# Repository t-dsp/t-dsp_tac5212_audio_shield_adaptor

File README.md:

# T-DSP TAC5212 Audio Shield Adaptor for Teensy 4.1

**Part of the [T-DSP](https://t-dsp.com) open modular audio platform.**

A compact carrier board (60.93mm × 26.46mm) that connects a [T-DSP TAC5212 audio module](https://github.com/t-dsp) and a [Teensy 4.1](https://www.pjrc.com/teensy/) together into a simple, USB-powered Teensy audio shield — with stereo line in/out, two onboard PDM MEMS microphones, USB Host, and SD card access.

| | |
|:---:|:---:|
|  |  |
|  |  |

**[View 3D Render Gallery](https://t-dsp.github.io/t-dsp_tac5212_audio_shield_adaptor/gallery.html)** -- interactive slideshow of all board views

## Assembled Hardware

| | |
|:---:|:---:|
|  |  |
| Top — TAC5212 module on the adaptor | Side — adaptor + Teensy 4.1 + TAC5212 module |

## What It Is

This is the simplest board in the T-DSP ecosystem. It is an **adaptor** — a small carrier PCB that brings together two modules:

- **[T-DSP TAC5212 module](https://github.com/t-dsp)** — the pro audio codec daughter board (plugs into the adaptor via headers)
- **[Teensy 4.1](https://www.pjrc.com/teensy/)** — ARM Cortex-M7 running the [Teensy Audio Library](https://www.pjrc.com/teensy/td_libs_Audio.html)

The result is a compact, bus-powered audio shield with stereo line I/O, two MEMS microphones, USB Host, and SD card access — no external power supply required.

## What You Need

| Item | Notes |
|------|-------|
| T-DSP TAC5212 audio module | Plugs into the adaptor's module connector |
| Teensy 4.1 | Socketed onto the adaptor's Teensy headers |
| This adaptor PCB | The carrier board documented here |

Power comes from the Teensy 4.1's USB connector — no external supply needed.

## Features

### Audio I/O
- **Stereo line input** -- via the TAC5212 module's ADC
- **Stereo line output** -- via the TAC5212 module's DAC
- **2× PDM MEMS microphones** -- Knowles SPK0641HT4H-1, speakerphone-grade, for voice capture or stereo room mics

### Connectivity
- **USB Host** -- USB-A host port for MIDI controllers, USB storage, and USB audio devices
- **SD card** -- Accessible via the Teensy 4.1's built-in SD slot

### Power
- **USB via Teensy 4.1** -- Bus-powered from the Teensy's USB port; no additional power input on this board

## Board Design

- **60.93mm × 26.46mm** PCB
- Designed around the T-DSP audio module board outline standard
- The TAC5212 module handles the entire analog signal path
- KiCad source files, full BOM, and CI-generated manufacturing outputs included
- Open source under CC BY-NC-SA 4.0

## Getting Started

### Hardware

1. Solder pin headers on your **Teensy 4.1** (if not already done)
2. Socket the Teensy 4.1 into the adaptor board headers
3. Plug the **TAC5212 module** into its connector on the adaptor
4. Connect your line-level audio source and output to the TAC5212 module's jacks
5. Connect USB to the Teensy 4.1 for power and optionally USB Audio

### Firmware

Working firmware lives in the **[T-DSP Software](https://github.com/t-dsp/t-dsp_software)** repository, in the [`projects/t-dsp_tac5212_audio_shield_adaptor`](https://github.com/t-dsp/t-dsp_software/tree/master/projects/t-dsp_tac5212_audio_shield_adaptor) folder. It's a PlatformIO project that gives you:

- **USB Audio class device** — the Teensy enumerates as a stereo soundcard on the host
- **Stereo playback** — host audio plays through the TAC5212 DAC out
- **PDM mic + line-in capture** — both onboard PDM mics and the line input are mixed into the host recording stream
- **Live monitoring** — toggle PDM mic and/or line input through the headphone output via simple serial commands
- **Host volume tracking** — the OS playback volume slider directly controls the TAC5212 DAC digital volume

To build and flash:

```bash
git clone https://github.com/t-dsp/t-dsp_software.git
cd t-dsp_software/projects/t-dsp_tac5212_audio_shield_adaptor
python -m platformio run --target upload
```

See the [project README](https://github.com/t-dsp/t-dsp_software/tree/master/projects/t-dsp_tac5212_audio_shield_adaptor) for the full setup walkthrough, audio routing diagram, and serial command reference. New to PlatformIO? Start with the [hello-world setup guide](https://github.com/t-dsp/t-dsp_software/tree/master/projects/hello-world).

View the design files in your browser with KiCanvas: [Schematic](https://kicanvas.org/?github=https://github.com/t-dsp/t-dsp_tac5212_audio_shield_adaptor/blob/main/t-dsp_tac5212_audio_shield_adaptor.kicad_sch) | [PCB](https://kicanvas.org/?github=https://github.com/t-dsp/t-dsp_tac5212_audio_shield_adaptor/blob/main/t-dsp_tac5212_audio_shield_adaptor.kicad_pcb)

## Project Files

| Directory | Contents |
|-----------|----------|
| `/3d_models/` | 3D models for PCB components |
| `/lib_fp/` | Custom KiCad footprint libraries |
| `/lib_sch/` | Custom KiCad schematic symbol libraries |
| `/manufacturing/` | CI-generated manufacturing outputs (gerbers, BOM, pick & place, PDFs) |
| `/pages/` | [3D Render Gallery](https://t-dsp.github.io/t-dsp_tac5212_audio_shield_adaptor/gallery.html), [Interactive BOM](https://t-dsp.github.io/t-dsp_tac5212_audio_shield_adaptor/ibom.html) |

## Manufacturing

Manufacturing files are generated automatically by [KiBot](https://github.com/INTI-CMNB/KiBot) on every push to `main` and on tagged releases via GitHub Actions.

To order:
1. Download the latest `t-dsp_tac5212_audio_shield_adaptor-manufacturing-vX.X.X.zip` from [Releases](https://github.com/t-dsp/t-dsp_tac5212_audio_shield_adaptor/releases)
2. Upload gerbers and drill files to your PCB fab (JLCPCB, PCBWay, etc.)
3. Use the BOM and CPL files for JLCPCB SMT assembly

## About T-DSP

T-DSP is an open modular audio platform built around the Teensy microcontroller and the [Teensy Audio Library](https://www.pjrc.com/teensy/td_libs_Audio.html). This adaptor is the simplest entry point — a small carrier that turns a Teensy 4.1 and a TAC5212 module into a working audio shield.

For a full desktop audio development platform with ESP32 UI, MIDI I/O, S/PDIF, RCA I/O, and multi-module TDM expansion, see the [T-DSP Desktop Pro](https://github.com/t-dsp/t-dsp_desktop_pro).

Learn more at [t-dsp.com](https://t-dsp.com).

## Status

Active development. If you build one, please open an issue or reach out.

## Contact

For consulting, custom audio hardware design, or commercial licensing, reach out via [LinkedIn](https://linkedin.com/in/jayshoe).

## License

[Creative Commons Attribution-NonCommercial-ShareAlike 4.0 International (CC BY-NC-SA 4.0)](https://creativecommons.org/licenses/by-nc-sa/4.0/)

Free to share and adapt for non-commercial purposes with attribution and same license on derivatives.

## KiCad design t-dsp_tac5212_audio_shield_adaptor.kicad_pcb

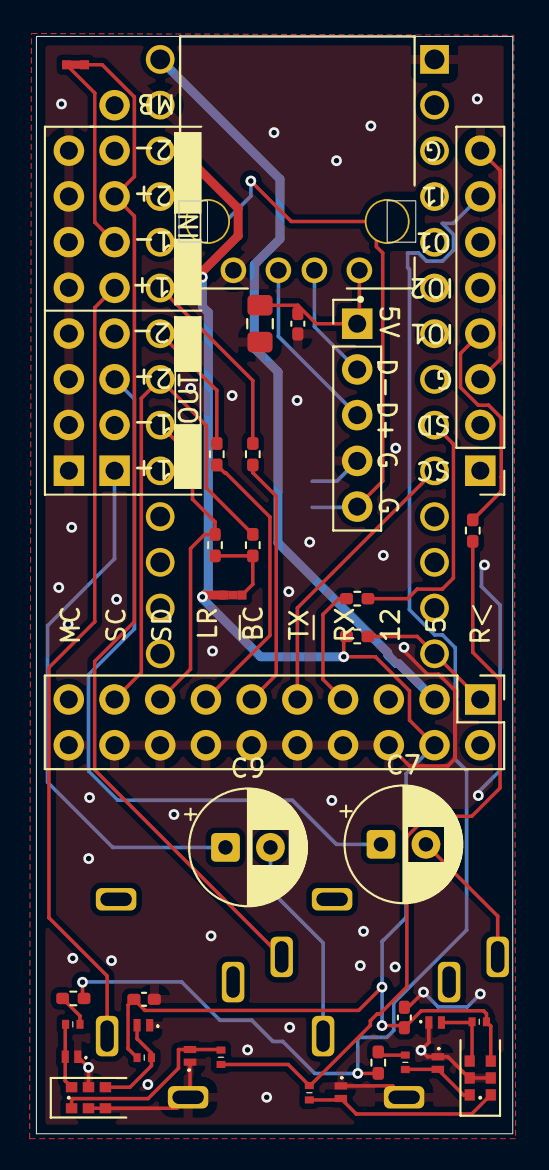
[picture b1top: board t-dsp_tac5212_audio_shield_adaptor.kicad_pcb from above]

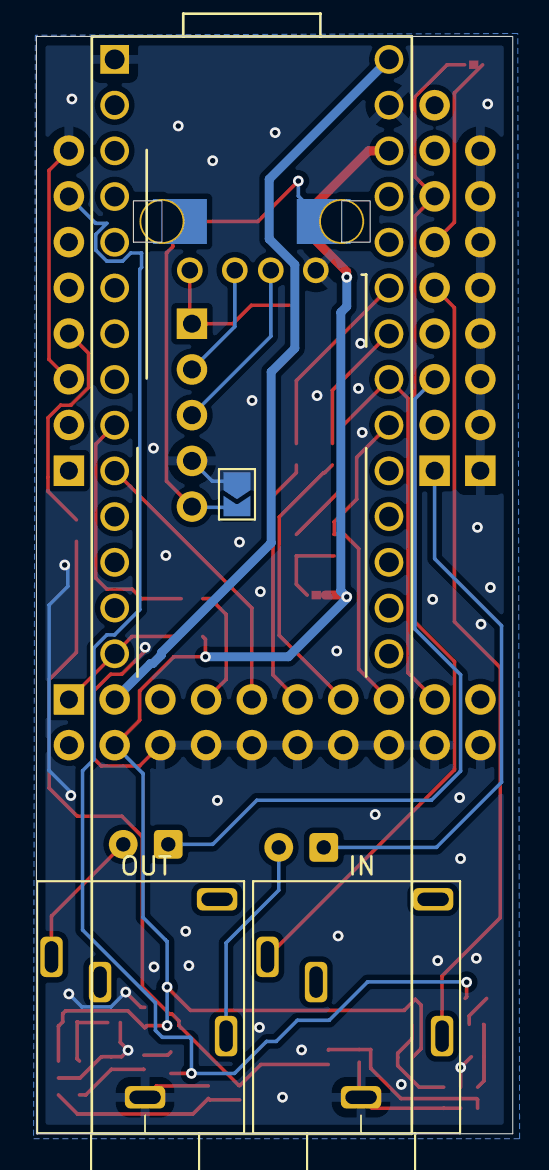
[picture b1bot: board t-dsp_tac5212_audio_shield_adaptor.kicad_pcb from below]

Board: 2 copper layers, 26.5 x 61.0 mm, 38 parts (4 on the bottom side), 36 nets.

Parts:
C1: 1 uF; C_0402_1005Metric_Pad0.74x0.62mm_HandSolder
C7, C9: 470 uF Electrolytic Audio-Grade; CP_Radial_D6.3mm_P2.50mm
C10, C40: 0.1uF; C_0402_1005Metric_Pad0.74x0.62mm_HandSolder
C33: 10 uF; C_0805_2012Metric_Pad1.15x1.40mm_HandSolder
D6, D7, D8, D9, D10, D11: ESD DIODE; PESD5V0F1BL_315
FB1, FB2, FB3, FB4, FB5, FB6: 600Ω@100MHz; BLM15AG601SN1D
G1: jumper; SolderJumper-2_P1.3mm_Open_TrianglePad1.0x1.5mm
HPTRS1, HPTRS2: 3.5mm TRS - 35RAPC3BH3; 35RAPC3BH3
J21: jumper; jumper_slice
MK1, MK2: MSM261DGT003
R3, R6, R9, R55, R56, R57: 49.9 ohm; R_0402_1005Metric_Pad0.72x0.64mm_HandSolder
R11: 10k; R_0402_1005Metric_Pad0.72x0.64mm_HandSolder
R12: 0 ohm; jumper_slice
R13, R14: 2.21k; R_0402_1005Metric_Pad0.72x0.64mm_HandSolder
U1: Teensy 4.1 - DEVKIT; Teensy41_simple
USBA1: USB A Host - TE 292303-5; TE_292303-5_USB_A_tight_fit
USB_HOST_1: header; USB_IN1
board_outline1: TAC5212 Module; audio_module_board_outline_final_minus-.66_mod_long

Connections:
3.3V: C10.1, C40.1, FB5.1, FB6.1, MK1.6 (SELECT), R11.1, R12.2, U1.46 (3V3), board_outline1.4 (3.3V)
5V: U1.48 (VIN), board_outline1.3 (5V)
7_OUT1A: R3.2, board_outline1.7 (DSP_DOUT)
8_IN1: U1.10 (8_TX2_IN1), board_outline1.9 (DSP_DIN)
35_TX8_RESET: R11.2, U1.14 (12_MISO_MQSL), board_outline1.1 (HELD_HIGH)
/AUDIO_IN1P: HPTRS2.5, board_outline1.29 (IN1P)
/AUDIO_IN2P: HPTRS2.2, J21.1, board_outline1.33 (IN2P)
/AUDIO_OUT2P: C7.1, board_outline1.25 (OUT2P)
/AUDIO_OUTP: C9.1, board_outline1.21 (OUTP)
BCLK1: R6.2, board_outline1.11 (BCLK)
GND: C1.2, C10.2, C33.2, C40.2, D6.1 (K), D7.1 (K), D8.1 (K), D9.1 (K), D10.1 (K), D11.1 (K), G1.1, HPTRS1.1, HPTRS2.1, MK1.2 (GND), MK1.5 (GND), MK2.2 (GND), MK2.5 (GND), MK2.6 (SELECT), U1.1 (GND), U1.47 (GND), USBA1.4 (GND), USB_HOST_1.4 (GND), board_outline1.6 (GNDD), board_outline1.8 (GNDD), board_outline1.10 (GNDD), board_outline1.12 (GNDD), board_outline1.14 (GNDD), board_outline1.16 (GNDD), board_outline1.18 (GNDD), board_outline1.20 (GNDD), board_outline1.22 (AGND), board_outline1.24 (AGND), board_outline1.26 (AGND), board_outline1.28 (AGND), board_outline1.30 (AGND), board_outline1.32 (AGND), board_outline1.34 (AGND), board_outline1.36 (AGND), board_outline1.39 (GNDD), board_outline1.44 (GNDD)
GPIGPI1: R56.1, R57.1, board_outline1.43 (GPI1)
GPIO1: FB3.2, FB4.2, R55.2
HOST_5V: C1.1, C33.1, USBA1.1 (VBUS), USB_HOST_1.1 (5V)
HOST_D1+: USBA1.3 (D+), USB_HOST_1.3 (D1+)
HOST_D1-: USBA1.2 (D-), USB_HOST_1.2 (D1-)
LRCK1: R9.2, board_outline1.13 (LRCK)
unnamed: C7.2, HPTRS1.2
unnamed: C9.2, HPTRS1.5
unnamed: D6.2 (A), FB5.2, MK1.1 (VDD)
unnamed: D7.2 (A), FB6.2, MK2.1 (VDD)
unnamed: D8.2 (A), FB2.2, MK2.3 (DATA)
unnamed: D9.2 (A), FB1.2, MK1.3 (DATA)
unnamed: D10.2 (A), FB3.1, MK2.4 (CLOCK)
unnamed: D11.2 (A), FB4.1, MK1.4 (CLOCK)
unnamed: FB1.1, R57.2
unnamed: FB2.1, R56.2
unnamed: R12.1, R13.2, R14.2
unnamed: R3.1, U1.9 (7_RX2_OUT1A)
unnamed: R9.1, U1.42 (20_A6_TX5_LRCLK1)
unnamed: R6.1, U1.43 (21_A7_RX5_BCLK1)
unnamed: R55.1, board_outline1.40 (GPIO1)
unnamed: J21.2, board_outline1.31 (IN1M)
SCL0: R13.1, U1.41 (19_A5_SCL), board_outline1.17 (SCL)
SDA0: R14.1, U1.40 (18_A4_SDA), board_outline1.15 (SDA)
USB_SHIELD2: G1.2, USBA1.5 (Shield), USB_HOST_1.5 (SHIELD)

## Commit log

2026-03-01 v0.01: Initial release - TAC5212 audio shield adaptor for Teensy 4.1
    Carrier board (60.93mm x 26.46mm) connecting the T-DSP TAC5212 audio
    module and Teensy 4.1 with stereo line in/out, dual PDM MEMS mics
    (SPK0641HT4H-1), USB Host, and SD card access. Bus-powered via Teensy USB-C.
2026-03-01 Fix: remove inner copper layers from pcb_pdf (2-layer board)
2026-03-02 v0.1: Finish routing, update board outline and revision
    - Complete PCB routing and zone fills
    - Add board outline footprint variants (-0.66mm offset)
    - Update USB-A footprint to KiCad 9.0 format
    - Fix schematic connections and capacitor orientation
    - Correct project filename metadata
    - Update 3D model
2026-03-10 update usb-a connector
2026-03-10 Update t-dsp_tac5212_audio_shield_adaptor.kicad_sch
    clean up BOM
2026-03-10 Update PCB layout
2026-03-14 Add new components, 3D models, and update PCB layout
    Add footprints and symbols for BLM15AG601SN1D, MSM261DGT003,
    PESD5V0F1BL_315, 35RAPC4BV4, and passive 0402 components.
    Add corresponding 3D models. Update schematic, PCB layout,
    and existing footprints.
2026-03-15 Fix ESD diode values and R13 value format for BOM correctness
2026-04-10 Add assembled hardware photos and link to firmware repo
    - New 'Assembled Hardware' section with top and side photos of the
    fully assembled stack (Teensy 4.1 + adaptor + TAC5212 module)
    - Replace placeholder firmware example with a link to the working
    firmware in t-dsp_software/projects/t-dsp_tac5212_audio_shield_adaptor,
    including a build/flash quickstart and feature summary
    Photos are hosted in the t-dsp_software repo (single source of truth)
